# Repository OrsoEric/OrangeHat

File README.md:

# OrangeHat
Raspberry Pi Hat

**TPS55386 Board**  
Dual buck from 2S to 4S LIPO to two 3.0A channels.  

**OrangeHat**  
Assembly

Demo OrangeHat installed on Maze Runner (click on image to see video on youtube)    

**OrangeHat Firmware**  
LCD Display (click on image to see video on youtube)  

Eight Servomotors Demo

https://github.com/user-attachments/assets/cbe1ea65-5b8f-492d-bec4-1e71fcff2395

**OrangeHat Software**  
NODE.JS Webserver video streaming and serial communication (click on image to see video on youtube)

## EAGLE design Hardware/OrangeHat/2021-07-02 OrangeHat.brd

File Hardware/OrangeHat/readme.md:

**FEATURES**  
- XT60 power connector
- TPS55386 Dual Buck two 5.2V3.0A channels. Reverse voltage protection. Passive and active overcurrent protection.
- Full power monitor. Three voltages, Three currents.
- Raspberry Pi GPIO (10pins) UART and RESET (for bootloader)
- AT4809 microcontroller with UPDI programming
- One user button. Two user LEDs-
- 16x2 LCD screen
- RS485 commuinication over 3.5mm Jack audio cables.
- 8x Servo channels
- Onboard Waveshare 10DOF IMU

**Schematics**  

**PCB Render**  
Render of PCB, Top and Bot side.  
  
Render of the gerbers files.  

**Microcontroller Pin Assignment Table**

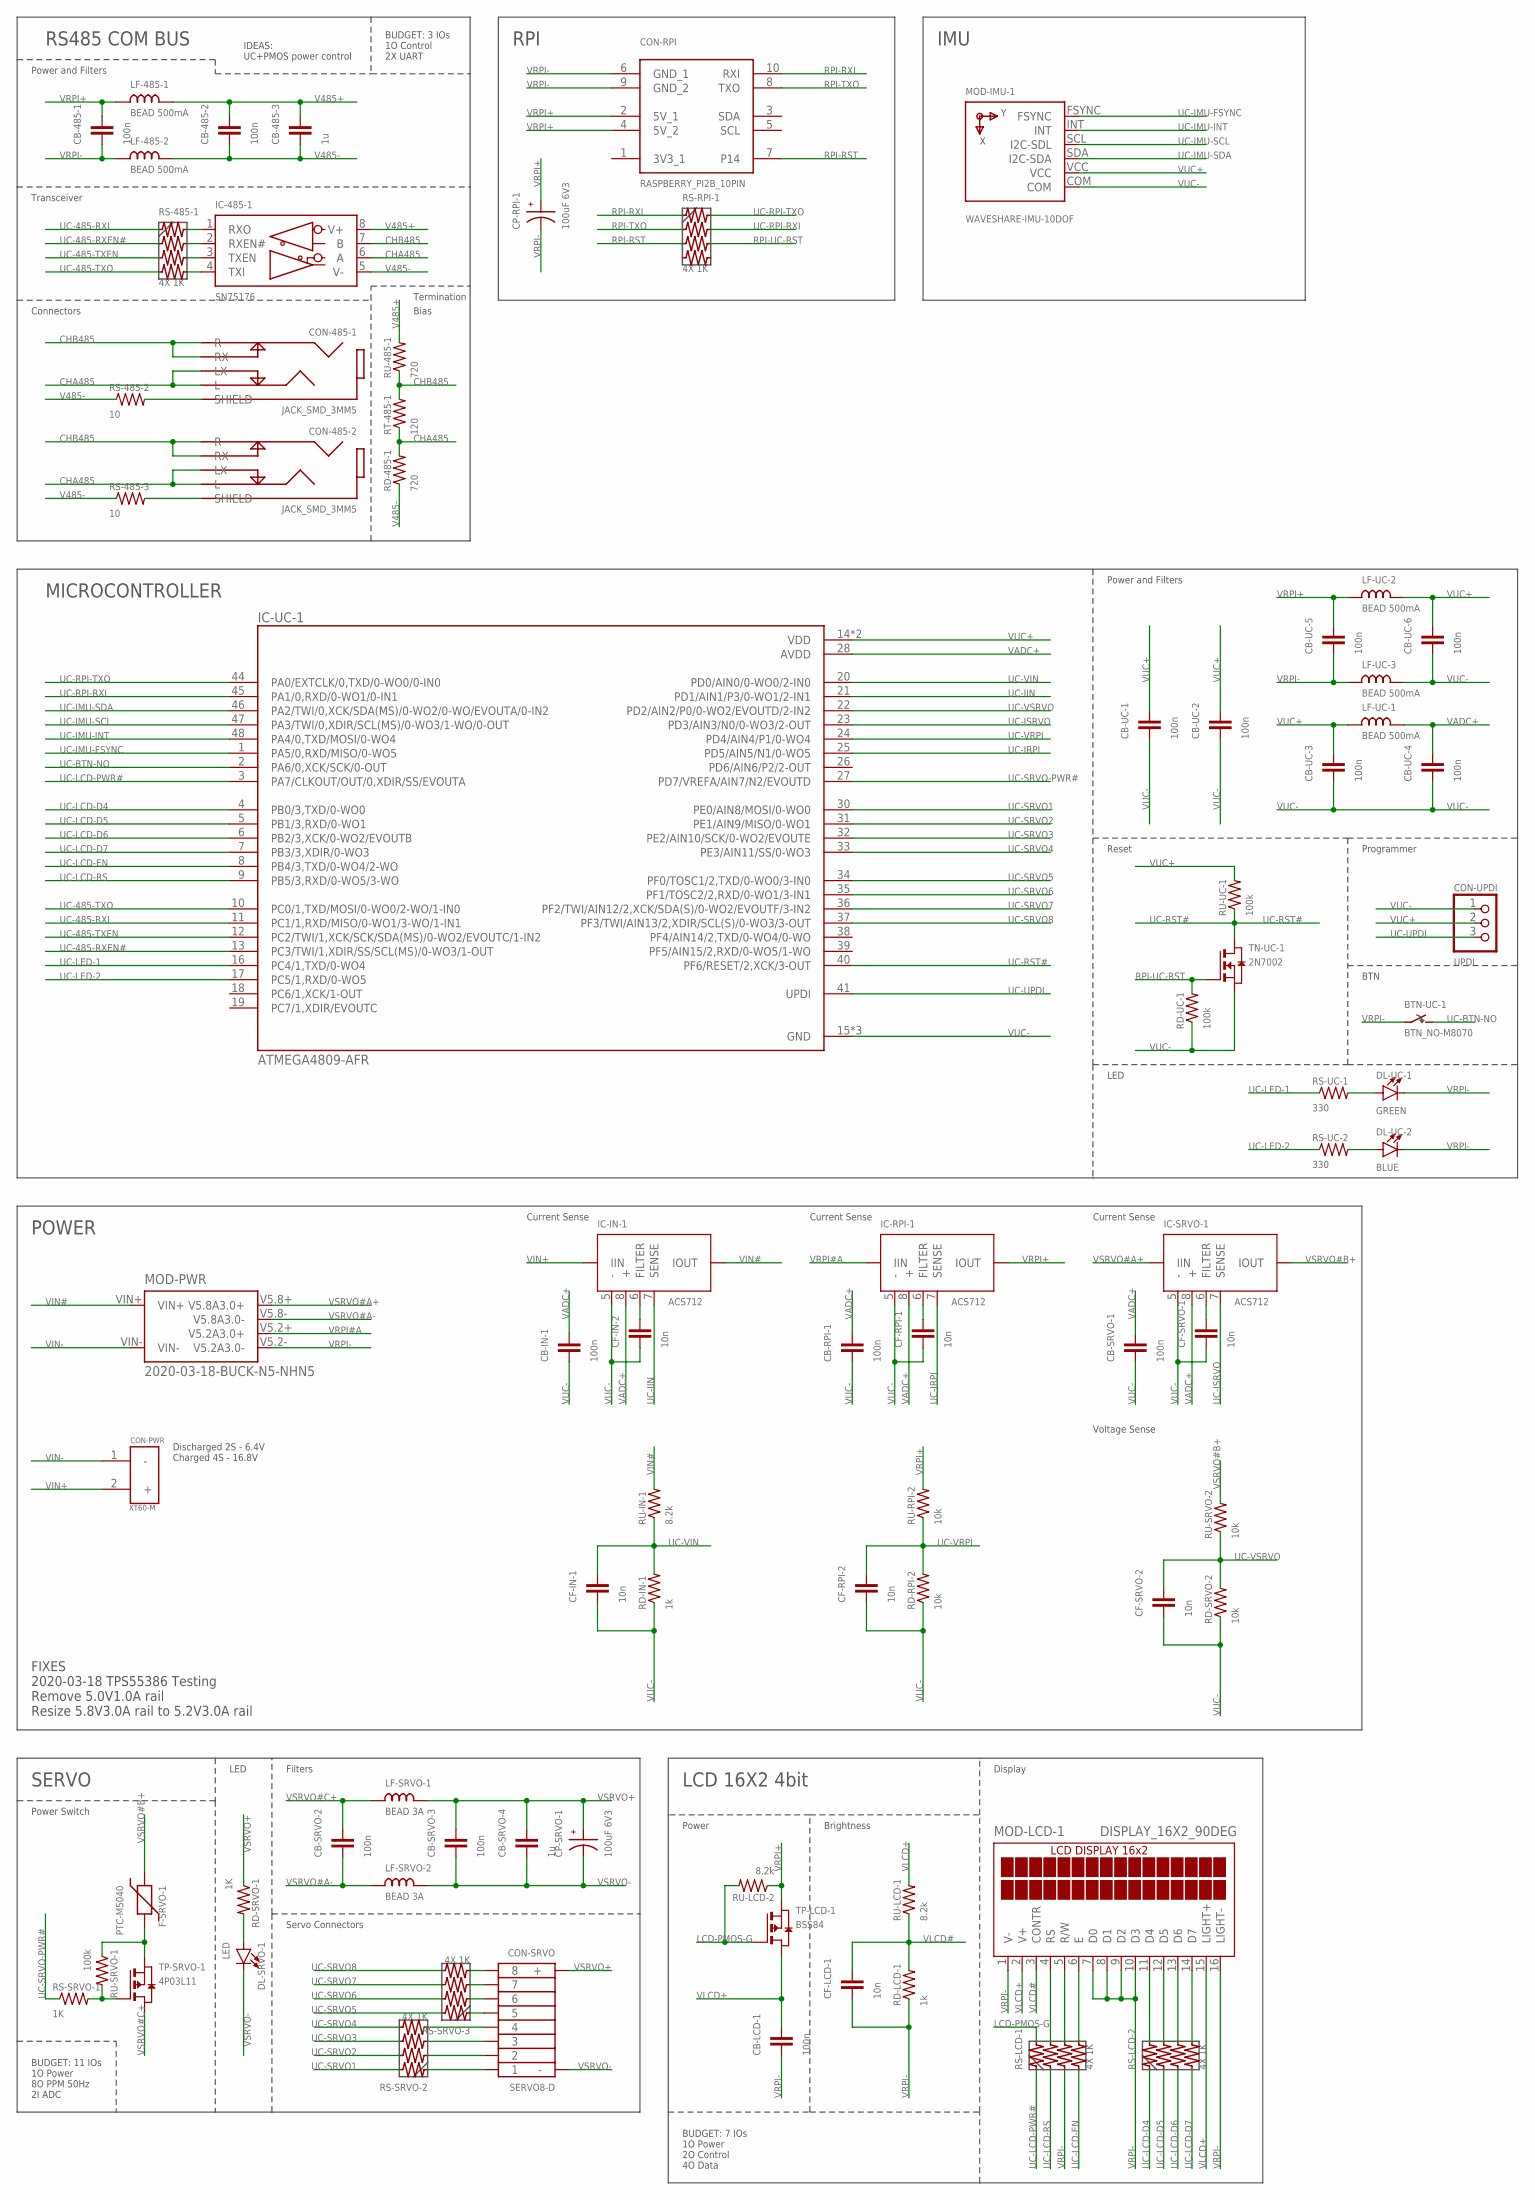
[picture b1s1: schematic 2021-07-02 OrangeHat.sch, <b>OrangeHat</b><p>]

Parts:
BTN-UC-1: BTN_NO-M8070; SMD_BTN_M8070
CB-485-1, CB-485-2: 100n; SMD-M2012
CB-485-3: 1u; SMD-M2012
CB-IN-1: 100n; SMD-M2012
CB-LCD-1: 100n; SMD-M2012
CB-RPI-1: 100n; SMD-M2012
CB-SRVO-1, CB-SRVO-2, CB-SRVO-3: 100n; SMD-M2012
CB-SRVO-4: 1u; SMD-M2012
CB-UC-1, CB-UC-2, CB-UC-3, CB-UC-4, CB-UC-5, CB-UC-6: 100n; SMD-M2012
CF-IN-1, CF-IN-2: 10n; SMD-M2012
CF-LCD-1: 10n; SMD-M2012
CF-RPI-1, CF-RPI-2: 10n; SMD-M2012
CF-SRVO-1, CF-SRVO-2: 10n; SMD-M2012
CON-485-1, CON-485-2: JACK_SMD_3MM5
CON-PWR: XT60-M; AMASS_XT60-M
CON-RPI: RASPBERRY_PI2B_10PIN
CON-SRVO: SERVO8-D; SERVO8#
CON-UPDI: UPDI; 1X03
CP-RPI-1: 100uF 6V3; E2,5-5
CP-SRVO-1: 100uF 6V3; E2,5-5
DL-SRVO-1: LED; SMD-M2012-POL
DL-UC-1: GREEN; SMD-M2012-POL
DL-UC-2: BLUE; SMD-M2012-POL
F-SRVO-1: PTC-M5040; SMD-M5040
IC-485-1: SN75176; DIL08
IC-IN-1: ACS712; SO8
IC-RPI-1: ACS712; SO8
IC-SRVO-1: ACS712; SO8
IC-UC-1: ATMEGA4809-AFR; QFP50P900X900X120-48N
LF-485-1, LF-485-2: BEAD 500mA; SMD-M2012
LF-SRVO-1, LF-SRVO-2: BEAD 3A; SMD-M2016
LF-UC-1, LF-UC-2, LF-UC-3: BEAD 500mA; SMD-M2012
MOD-IMU-1: WAVESHARE-IMU-10DOF
MOD-LCD-1: DISPLAY_16X2_90DEG
MOD-PWR: 2020-03-18-BUCK-N5-NHN5; 2020-03-18-BUCK-NHN5
RD-485-1: 720; TH-2MM54-V
RD-IN-1: 1k; SMD-M2012
RD-LCD-1: 1k; SMD-M2012
RD-RPI-2: 10k; SMD-M2012
RD-SRVO-1: 1K; SMD-M2012
RD-SRVO-2: 10k; SMD-M2012
RD-UC-1: 100k; SMD-M2012
RS-485-1: 4X 1K; RAC1206
RS-485-2, RS-485-3: 10; SMD-M2012
RS-LCD-1, RS-LCD-2: 4X 1K; RAC1206
RS-RPI-1: 4X 1K; RAC1206
RS-SRVO-1: 1K; SMD-M2012
RS-SRVO-2, RS-SRVO-3: 4X 1K; RAC1206
RS-UC-1, RS-UC-2: 330; SMD-M2012
RT-485-1: 120; TH-2MM54-V
RU-485-1: 720; TH-2MM54-V
RU-IN-1: 8.2k; SMD-M2012
RU-LCD-1, RU-LCD-2: 8.2k; SMD-M2012
RU-RPI-2: 10k; SMD-M2012
RU-SRVO-1: 100k; SMD-M2012
RU-SRVO-2: 10k; SMD-M2012
RU-UC-1: 100k; SMD-M2012
TN-UC-1: 2N7002; SOT23
TP-LCD-1: BSS84; SOT23
TP-SRVO-1: 4P03L11; TO252

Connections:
3V3_1: CON-RPI.1 (3V3_1)
CHA485: CON-485-1.L, CON-485-1.LX, CON-485-2.L, CON-485-2.LX, IC-485-1.6 (A), RD-485-1.2, RT-485-1.1
CHB485: CON-485-1.R, CON-485-1.RX, CON-485-2.R, CON-485-2.RX, IC-485-1.7 (B), RT-485-1.2, RU-485-1.1
LCD-PMOS-G: RS-LCD-1.1B, RU-LCD-2.2, TP-LCD-1.1 (G)
unnamed: CF-RPI-1.2, IC-RPI-1.6 (FILTER)
unnamed: CF-IN-2.2, IC-IN-1.6 (FILTER)
unnamed: MOD-LCD-1.5 (R/W), RS-LCD-1.3B
unnamed: DL-UC-1.+, RS-UC-1.2
unnamed: RS-SRVO-1.2, RU-SRVO-1.2, TP-SRVO-1.1 (G)
unnamed: F-SRVO-1.2, RU-SRVO-1.1, TP-SRVO-1.2 (S)
unnamed: MOD-LCD-1.4 (RS), RS-LCD-1.2B
unnamed: MOD-LCD-1.6 (E), RS-LCD-1.4B
unnamed: MOD-LCD-1.11 (D4), RS-LCD-2.1B
unnamed: MOD-LCD-1.12 (D5), RS-LCD-2.2B
unnamed: MOD-LCD-1.13 (D6), RS-LCD-2.3B
unnamed: MOD-LCD-1.14 (D7), RS-LCD-2.4B
unnamed: DL-UC-2.+, RS-UC-2.2
unnamed: IC-485-1.1 (RXO), RS-485-1.1B
unnamed: IC-485-1.2 (RXEN#), RS-485-1.2B
unnamed: CF-SRVO-1.2, IC-SRVO-1.6 (FILTER)
unnamed: DL-SRVO-1.+, RD-SRVO-1.2
unnamed: CON-SRVO.8, RS-SRVO-3.4A
unnamed: CON-SRVO.7, RS-SRVO-3.3A
unnamed: CON-SRVO.6, RS-SRVO-3.2A
unnamed: CON-SRVO.5, RS-SRVO-3.1A
unnamed: CON-SRVO.4, RS-SRVO-2.4A
unnamed: CON-SRVO.3, RS-SRVO-2.3A
unnamed: CON-SRVO.2, RS-SRVO-2.2A
unnamed: CON-SRVO.1, RS-SRVO-2.1A
unnamed: IC-485-1.3 (TXEN), RS-485-1.3B
unnamed: IC-485-1.4 (TXI), RS-485-1.4B
unnamed: CON-485-1.SHIELD, RS-485-2.2
unnamed: CON-485-2.SHIELD, RS-485-3.2
RPI-RST: CON-RPI.7 (P14), RS-RPI-1.3A
RPI-RXI: CON-RPI.10 (RXI), RS-RPI-1.1A
RPI-TXO: CON-RPI.8 (TXO), RS-RPI-1.2A
RPI-UC-RST: RD-UC-1.2, RS-RPI-1.3B, TN-UC-1.1 (G)
UC-485-RXEN#: IC-UC-1.13 (PC3/TWI/1,XDIR/SS/SCL(MS)/0-WO3/1-OUT), RS-485-1.2A
UC-485-RXI: IC-UC-1.11 (PC1/1,RXD/MISO/0-WO1/3-WO/1-IN1), RS-485-1.1A
UC-485-TXEN: IC-UC-1.12 (PC2/TWI/1,XCK/SCK/SDA(MS)/0-WO2/EVOUTC/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), RS-485-1.3A
UC-485-TXO: IC-UC-1.10 (PC0/1,TXD/MOSI/0-WO0/2-WO/1-IN0), RS-485-1.4A
UC-BTN-NO: BTN-UC-1.2B, BTN-UC-1.3B, IC-UC-1.2 (PA6/0,XCK/SCK/0-OUT)
UC-IIN: IC-IN-1.7 (SENSE), IC-UC-1.21 (PD1/AIN1/P3/0-WO1/2-IN1)
UC-IMU-FSYNC: IC-UC-1.1 (PA5/0,RXD/MISO/0-WO5), MOD-IMU-1.FSYNC
UC-IMU-INT: IC-UC-1.48 (PA4/0,TXD/MOSI/0-WO4), MOD-IMU-1.INT
UC-IMU-SCL: IC-UC-1.47 (PA3/TWI/0,XDIR/SCL(MS)/0-WO3/1-WO/0-OUT), MOD-IMU-1.SCL (I2C-SDL)
UC-IMU-SDA: IC-UC-1.46 (PA2/TWI/0,XCK/SDA(MS)/0-WO2/0-WO/EVOUTA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), MOD-IMU-1.SDA (I2C-SDA)
UC-IRPI: IC-RPI-1.7 (SENSE), IC-UC-1.25 (PD5/AIN5/N1/0-WO5)
UC-ISRVO: IC-SRVO-1.7 (SENSE), IC-UC-1.23 (PD3/AIN3/N0/0-WO3/2-OUT)
UC-LCD-D4: IC-UC-1.4 (PB0/3,TXD/0-WO0), RS-LCD-2.1A
UC-LCD-D5: IC-UC-1.5 (PB1/3,RXD/0-WO1), RS-LCD-2.2A
UC-LCD-D6: IC-UC-1.6 (PB2/3,XCK/0-WO2/EVOUTB), RS-LCD-2.3A
UC-LCD-D7: IC-UC-1.7 (PB3/3,XDIR/0-WO3), RS-LCD-2.4A
UC-LCD-EN: IC-UC-1.8 (PB4/3,TXD/0-WO4/2-WO), RS-LCD-1.4A
UC-LCD-PWR#: IC-UC-1.3 (PA7/CLKOUT/OUT/0,XDIR/SS/EVOUTA), RS-LCD-1.1A
UC-LCD-RS: IC-UC-1.9 (PB5/3,RXD/0-WO5/3-WO), RS-LCD-1.2A
UC-LED-1: IC-UC-1.16 (PC4/1,TXD/0-WO4), RS-UC-1.1
UC-LED-2: IC-UC-1.17 (PC5/1,RXD/0-WO5), RS-UC-2.1
UC-RPI-RXI: IC-UC-1.45 (PA1/0,RXD/0-WO1/0-IN1), RS-RPI-1.2B
UC-RPI-TXO: IC-UC-1.44 (PA0/EXTCLK/0,TXD/0-WO0/0-IN0), RS-RPI-1.1B
UC-RST#: IC-UC-1.40 (PF6/RESET/2,XCK/3-OUT), RU-UC-1.1, TN-UC-1.3 (D)
UC-SRVO1: IC-UC-1.30 (PE0/AIN8/MOSI/0-WO0), RS-SRVO-2.1B
UC-SRVO2: IC-UC-1.31 (PE1/AIN9/MISO/0-WO1), RS-SRVO-2.2B
UC-SRVO3: IC-UC-1.32 (PE2/AIN10/SCK/0-WO2/EVOUTE), RS-SRVO-2.3B
UC-SRVO4: IC-UC-1.33 (PE3/AIN11/SS/0-WO3), RS-SRVO-2.4B
UC-SRVO5: IC-UC-1.34 (PF0/TOSC1/2,TXD/0-WO0/3-IN0), RS-SRVO-3.1B
UC-SRVO6: IC-UC-1.35 (PF1/TOSC2/2,RXD/0-WO1/3-IN1), RS-SRVO-3.2B
UC-SRVO7: IC-UC-1.36 (PF2/TWI/AIN12/2,XCK/SDA(S)/0-WO2/EVOUTF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), RS-SRVO-3.3B
UC-SRVO8: IC-UC-1.37 (PF3/TWI/AIN13/2,XDIR/SCL(S)/0-WO3/3-OUT), RS-SRVO-3.4B
UC-SRVO-PWR#: IC-UC-1.27 (PD7/VREFA/AIN7/N2/EVOUTD), RS-SRVO-1.1
UC-UPDI: CON-UPDI.3, IC-UC-1.41 (UPDI)
UC-VIN: CF-IN-1.2, IC-UC-1.20 (PD0/AIN0/0-WO0/2-IN0), RD-IN-1.2, RU-IN-1.1
UC-VRPI: CF-RPI-2.2, IC-UC-1.24 (PD4/AIN4/P1/0-WO4), RD-RPI-2.2, RU-RPI-2.1
UC-VSRVO: CF-SRVO-2.2, IC-UC-1.22 (PD2/AIN2/P0/0-WO2/EVOUTD/2-IN2), RD-SRVO-2.2, RU-SRVO-2.1
V485+: CB-485-2.2, CB-485-3.2, IC-485-1.8 (V+), LF-485-1.2, RU-485-1.2
V485-: CB-485-2.1, CB-485-3.1, IC-485-1.5 (V-), LF-485-2.2, RD-485-1.1, RS-485-2.1, RS-485-3.1
VADC+: CB-IN-1.2, CB-RPI-1.2, CB-SRVO-1.2, CB-UC-4.2, IC-IN-1.8 (+), IC-RPI-1.8 (+), IC-SRVO-1.8 (+), IC-UC-1.28 (AVDD), LF-UC-1.2
VIN#: IC-IN-1.3 (IOUT), IC-IN-1.4 (IOUT), MOD-PWR.VIN+, RU-IN-1.2
VIN+: CON-PWR.2 (+), IC-IN-1.1 (IIN), IC-IN-1.2 (IIN)
VIN-: CON-PWR.1 (-), MOD-PWR.VIN-
VLCD#: CF-LCD-1.2, MOD-LCD-1.3 (CONTR), RD-LCD-1.2, RU-LCD-1.1
VLCD+: CB-LCD-1.2, MOD-LCD-1.2 (V+), MOD-LCD-1.15 (LIGHT+), RU-LCD-1.2, TP-LCD-1.3 (D)
VRPI#A: IC-RPI-1.1 (IIN), IC-RPI-1.2 (IIN), MOD-PWR.V5.2+ (V5.2A3.0+)
VRPI+: CB-485-1.2, CB-UC-5.2, CON-RPI.2 (5V_1), CON-RPI.4 (5V_2), CP-RPI-1.+, IC-RPI-1.3 (IOUT), IC-RPI-1.4 (IOUT), LF-485-1.1, LF-UC-2.1, RU-LCD-2.1, RU-RPI-2.2, TP-LCD-1.2 (S)
VRPI-: BTN-UC-1.1A, BTN-UC-1.4A, CB-485-1.1, CB-LCD-1.1, CB-UC-5.1, CF-LCD-1.1, CON-RPI.6 (GND_1), CON-RPI.9 (GND_2), CP-RPI-1.-, DL-UC-1.-, DL-UC-2.-, LF-485-2.1, LF-UC-3.1, MOD-LCD-1.1 (V-), MOD-LCD-1.7 (D0), MOD-LCD-1.8 (D1), MOD-LCD-1.9 (D2), MOD-LCD-1.10 (D3), MOD-LCD-1.16 (LIGHT-), MOD-PWR.V5.2- (V5.2A3.0-), RD-LCD-1.1, RS-LCD-1.3A
VSRVO#A+: IC-SRVO-1.1 (IIN), IC-SRVO-1.2 (IIN), MOD-PWR.V5.8+ (V5.8A3.0+)
VSRVO#A-: CB-SRVO-2.1, LF-SRVO-2.1, MOD-PWR.V5.8- (V5.8A3.0-)
VSRVO#B+: F-SRVO-1.1, IC-SRVO-1.3 (IOUT), IC-SRVO-1.4 (IOUT), RU-SRVO-2.2
VSRVO#C+: CB-SRVO-2.2, LF-SRVO-1.1, TP-SRVO-1.3 (D)
VSRVO+: CB-SRVO-3.2, CB-SRVO-4.2, CON-SRVO.1+ (+), CON-SRVO.2+ (+), CON-SRVO.3+ (+), CON-SRVO.4+ (+), CON-SRVO.5+ (+), CON-SRVO.6+ (+), CON-SRVO.7+ (+), CON-SRVO.8+ (+), CP-SRVO-1.+, LF-SRVO-1.2, RD-SRVO-1.1
VSRVO-: CB-SRVO-3.1, CB-SRVO-4.1, CON-SRVO.1- (-), CON-SRVO.2- (-), CON-SRVO.3- (-), CON-SRVO.4- (-), CON-SRVO.5- (-), CON-SRVO.6- (-), CON-SRVO.7- (-), CON-SRVO.8- (-), CP-SRVO-1.-, DL-SRVO-1.-, LF-SRVO-2.2
VUC+: CB-UC-1.2, CB-UC-2.2, CB-UC-3.2, CB-UC-6.2, CON-UPDI.2, IC-UC-1.14 (VDD), IC-UC-1.42 (VDD), LF-UC-1.1, LF-UC-2.2, MOD-IMU-1.VCC, RU-UC-1.2
VUC-: CB-IN-1.1, CB-RPI-1.1, CB-SRVO-1.1, CB-UC-1.1, CB-UC-2.1, CB-UC-3.1, CB-UC-4.1, CB-UC-6.1, CF-IN-1.1, CF-IN-2.1, CF-RPI-1.1, CF-RPI-2.1, CF-SRVO-1.1, CF-SRVO-2.1, CON-UPDI.1, IC-IN-1.5 (-), IC-RPI-1.5 (-), IC-SRVO-1.5 (-), IC-UC-1.15 (GND), IC-UC-1.29 (GND), IC-UC-1.43 (GND), LF-UC-3.2, MOD-IMU-1.COM, RD-IN-1.1, RD-RPI-2.1, RD-SRVO-2.1, RD-UC-1.1, TN-UC-1.2 (S)

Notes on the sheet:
LCD 16X2 4bit
Power
Brightness
Display
BUDGET: 7 IOs 1O Power 2O Control 4O Data
SERVO
BUDGET: 11 IOs 1O Power 8O PPM 50Hz 2I ADC
Servo Connectors
Power Switch
Filters
Current Sense
Voltage Sense
LED
RS485 COM BUS
Power and Filters
Transceiver
Connectors
Termination
Bias
BUDGET: 3 IOs 1O Control 2X UART
IDEAS: UC+PMOS power control
MICROCONTROLLER
Reset
RPI
POWER
Programmer
FIXES 2020-03-18 TPS55386 Testing Remove 5.0V1.0A rail Resize 5.8V3.0A rail to 5.2V3.0A rail
BTN
IMU
Discharged 2S - 6.4V Charged 4S - 16.8V

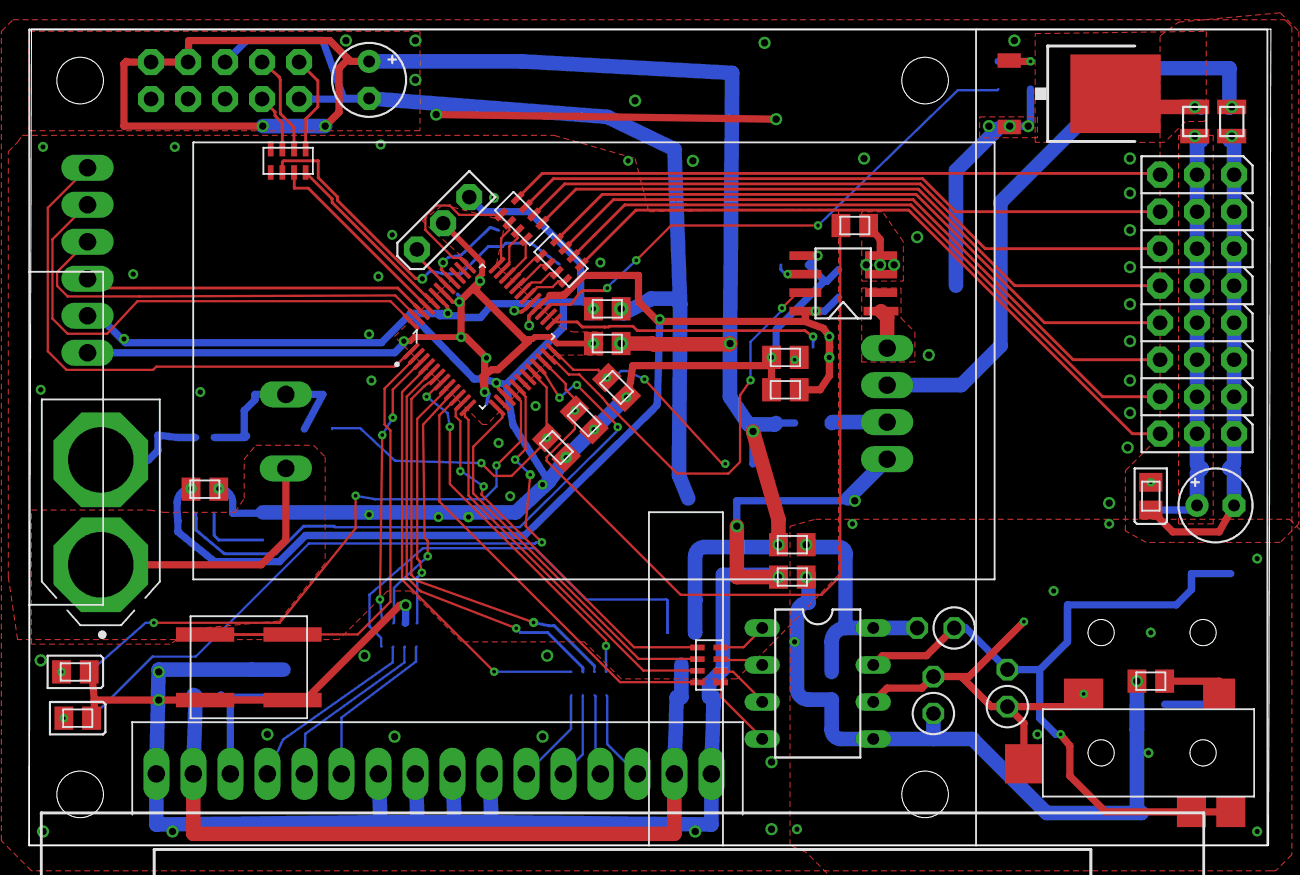
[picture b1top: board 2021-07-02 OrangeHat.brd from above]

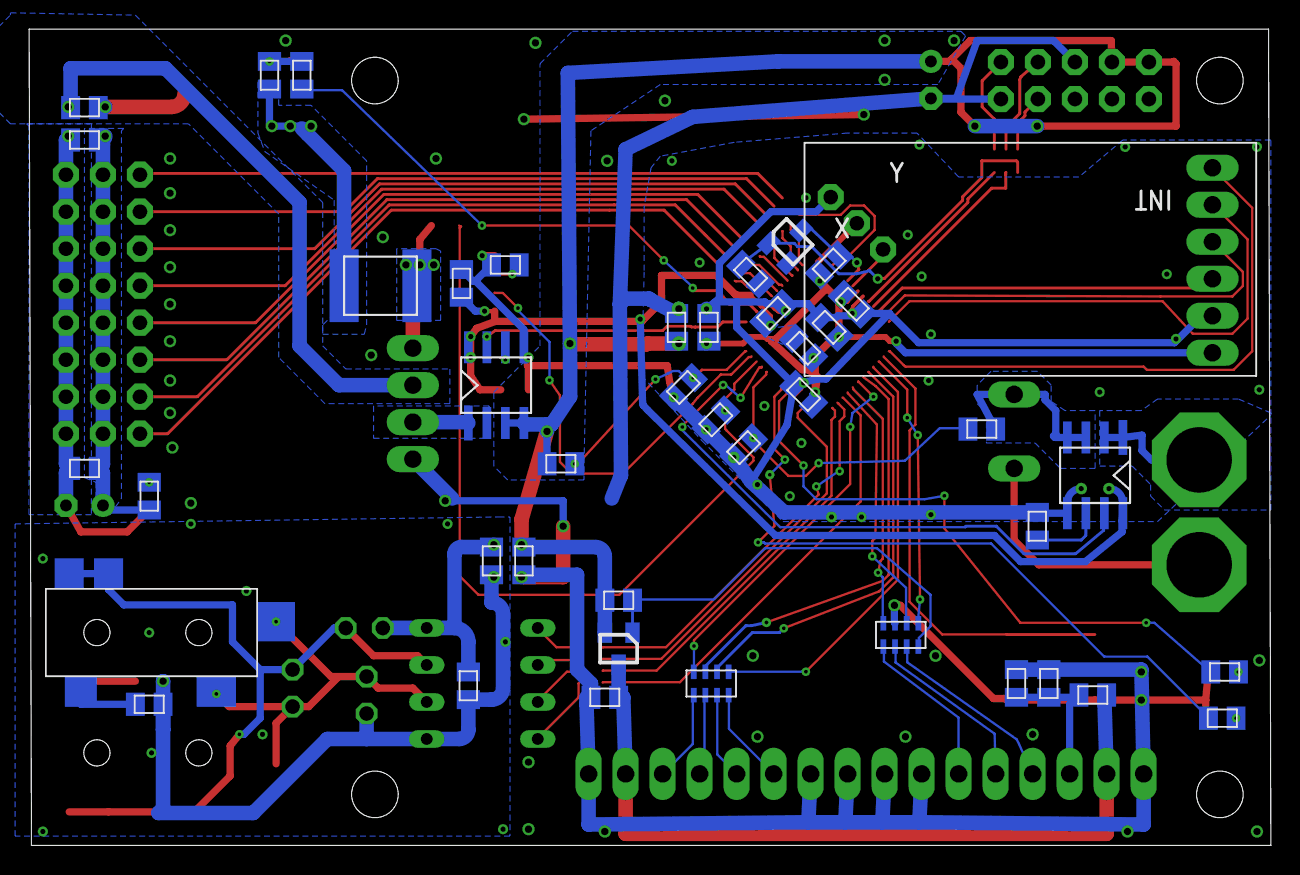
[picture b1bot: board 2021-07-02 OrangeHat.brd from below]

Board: 2 copper layers, 85.2 x 56.0 mm, 83 parts (43 on the bottom side), 92 nets.

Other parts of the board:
U$1: SIGNATURE_ADROBOT_SMALL
U$2: SIGNATURE_ORANGEBOT_SMALL

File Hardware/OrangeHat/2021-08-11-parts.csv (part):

"Part";"Value";"Device";"Package";"Description";"AVAILABILITY";"DESCRIPTION";"MF";"MP";"MPN";"OC_FARNELL";"OC_NEWARK";"PACKAGE";"PRICE";
"BTN-UC-1";"BTN_NO-M8070";"BTN_NO-M8070";"SMD_BTN_M8070";"Push Button";"";"";"";"";"";"";"";"";"";
"CB-485-1";"100n";"C-NPOL";"SMD-M2012";"CAPACITOR, European symbol";"";"";"";"";"";"";"";"";"";
"CB-485-2";"100n";"C-NPOL";"SMD-M2012";"CAPACITOR, European symbol";"";"";"";"";"";"";"";"";"";
"CB-485-3";"1u";"C-NPOL";"SMD-M2012";"CAPACITOR, European symbol";"";"";"";"";"";"";"";"";"";
"CB-IN-1";"100n";"C-NPOL";"SMD-M2012";"CAPACITOR, European symbol";"";"";"";"";"";"";"";"";"";
"CB-LCD-1";"100n";"C-NPOL";"SMD-M2012";"CAPACITOR, European symbol";"";"";"";"";"";"";"";"";"";
"CB-RPI-1";"100n";"C-NPOL";"SMD-M2012";"CAPACITOR, European symbol";"";"";"";"";"";"";"";"";"";
"CB-SRVO-1";"100n";"C-NPOL";"SMD-M2012";"CAPACITOR, European symbol";"";"";"";"";"";"";"";"";"";
"CB-SRVO-2";"100n";"C-NPOL";"SMD-M2012";"CAPACITOR, European symbol";"";"";"";"";"";"";"";"";"";
"CB-SRVO-3";"100n";"C-NPOL";"SMD-M2012";"CAPACITOR, European symbol";"";"";"";"";"";"";"";"";"";
"CB-SRVO-4";"1u";"C-NPOL";"SMD-M2012";"CAPACITOR, European symbol";"";"";"";"";"";"";"";"";"";
"CB-UC-1";"100n";"C-NPOL";"SMD-M2012";"CAPACITOR, European symbol";"";"";"";"";"";"";"";"";"";
"CB-UC-2";"100n";"C-NPOL";"SMD-M2012";"CAPACITOR, European symbol";"";"";"";"";"";"";"";"";"";
"CB-UC-3";"100n";"C-NPOL";"SMD-M2012";"CAPACITOR, European symbol";"";"";"";"";"";"";"";"";"";
"CB-UC-4";"100n";"C-NPOL";"SMD-M2012";"CAPACITOR, European symbol";"";"";"";"";"";"";"";"";"";
"CB-UC-5";"100n";"C-NPOL";"SMD-M2012";"CAPACITOR, European symbol";"";"";"";"";"";"";"";"";"";
"CB-UC-6";"100n";"C-NPOL";"SMD-M2012";"CAPACITOR, European symbol";"";"";"";"";"";"";"";"";"";
"CF-IN-1";"10n";"C-NPOL";"SMD-M2012";"CAPACITOR, European symbol";"";"";"";"";"";"";"";"";"";
"CF-IN-2";"10n";"C-NPOL";"SMD-M2012";"CAPACITOR, European symbol";"";"";"";"";"";"";"";"";"";
"CF-LCD-1";"10n";"C-NPOL";"SMD-M2012";"CAPACITOR, European symbol";"";"";"";"";"";"";"";"";"";
"CF-RPI-1";"10n";"C-NPOL";"SMD-M2012";"CAPACITOR, European symbol";"";"";"";"";"";"";"";"";"";
"CF-RPI-2";"10n";"C-NPOL";"SMD-M2012";"CAPACITOR, European symbol";"";"";"";"";"";"";"";"";"";
"CF-SRVO-1";"10n";"C-NPOL";"SMD-M2012";"CAPACITOR, European symbol";"";"";"";"";"";"";"";"";"";
"CF-SRVO-2";"10n";"C-NPOL";"SMD-M2012";"CAPACITOR, European symbol";"";"";"";"";"";"";"";"";"";
"CON-485-1";"JACK_SMD_3MM5";"JACK_SMD_3MM5";"JACK_SMD_3MM5";"Jack 3.5mm";"";"";"";"";"";"";"";"";"";
"CON-485-2";"JACK_SMD_3MM5";"JACK_SMD_3MM5";"JACK_SMD_3MM5";"Jack 3.5mm";"";"";"";"";"";"";"";"";"";
"CON-PWR";"XT60-M";"XT60-M";"AMASS_XT60-M";"DC supply; XT60; male; PIN:2; for cable; soldered; 60A; 500V";"Unavailable";" ";"AMASS";"XT60-M";"";"";"";"Package Analog Devices";"None";
"CON-RPI";"RASPBERRY_PI2B_10PIN";"RASPBERRY_PI2B_10PIN";"RASPBERRY_PI2B_10PIN";"Raspberry Pi 2B/3B Hat Footprint";"";"";"";"";"";"";"";"";"";
"CON-SRVO";"SERVO8-D";"SERVO8-D";"SERVO8#";"SERVO";"";"";"";"";"";"";"";"";"";
"CON-UPDI";"UPDI";"PINHD-1X3";"1X03";"PIN HEADER";"";"";"";"";"";"";"";"";"";
"CP-RPI-1";"100uF 6V3";"C-POLE2.5-5";"E2,5-5";"POLARIZED CAPACITOR, American symbol";"";"";"";"";"";"";"";"";"";
"CP-SRVO-1";"100uF 6V3";"C-POLE2.5-5";"E2,5-5";"POLARIZED CAPACITOR, American symbol";"";"";"";"";"";"";"";"";"";
"DL-SRVO-1";"LED";"LED";"SMD-M2012-POL";"Standard LED";"";"";"";"";"";"";"";"";"";
"DL-UC-1";"GREEN";"LED";"SMD-M2012-POL";"Standard LED";"";"";"";"";"";"";"";"";"";
"DL-UC-2";"BLUE";"LED";"SMD-M2012-POL";"Standard LED";"";"";"";"";"";"";"";"";"";
"F-SRVO-1";"PTC-M5040";"PTC-M5040";"SMD-M5040";"Resettable Fuse PTC";"";"";"";"";"";"";"";"";"";
"IC-485-1";"SN75176";"RS485";"DIL08";"RS485 TRANSEIVER";"";"";"";"";"MAX481CPA+";"unknown";"99K3445";"";"";
"IC-IN-1";"ACS712";"ACS712";"SO8";"ACS712-{X}";"";"";"";"";"";"";"";"";"";
"IC-RPI-1";"ACS712";"ACS712";"SO8";"ACS712-{X}";"";"";"";"";"";"";"";"";"";
"IC-SRVO-1";"ACS712";"ACS712";"SO8";"ACS712-{X}";"";"";"";"";"";"";"";"";"";
"IC-UC-1";"ATMEGA4809-AFR";"ATMEGA4809-AFR";"QFP50P900X900X120-48N";"20MHz 48KB TQFP48 Ind 125C Green T&R";"Unavailable";" 20MHz 48KB TQFP48 Ind 125C Green T&R ";"Microchip";"ATMEGA4809-AFR";"";"";"";"TQFP-48 Microchip";"None";
"LF-485-1";"BEAD 500mA";"L-M2012";"SMD-M2012";"INDUCTOR, American symbol";"";"";"";"";"";"";"";"";"";
"LF-485-2";"BEAD 500mA";"L-M2012";"SMD-M2012";"INDUCTOR, American symbol";"";"";"";"";"";"";"";"";"";
"LF-SRVO-1";"BEAD 3A";"L-M2016";"SMD-M2016";"INDUCTOR, American symbol";"";"";"";"";"";"";"";"";"";
"LF-SRVO-2";"BEAD 3A";"L-M2016";"SMD-M2016";"INDUCTOR, American symbol";"";"";"";"";"";"";"";"";"";
"LF-UC-1";"BEAD 500mA";"L-M2012";"SMD-M2012";"INDUCTOR, American symbol";"";"";"";"";"";"";"";"";"";
"LF-UC-2";"BEAD 500mA";"L-M2012";"SMD-M2012";"INDUCTOR, American symbol";"";"";"";"";"";"";"";"";"";
"LF-UC-3";"BEAD 500mA";"L-M2012";"SMD-M2012";"INDUCTOR, American symbol";"";"";"";"";"";"";"";"";"";
"MOD-IMU-1";"WAVESHARE-IMU-10DOF";"WAVESHARE-IMU-10DOF";"WAVESHARE-IMU-10DOF";"WaveShare IMU 10DOF";"";"";"";"";"";"";"";"";"";
"MOD-LCD-1";"DISPLAY_16X2_90DEG";"DISPLAY_16X2_90DEG";"DISPLAY_16X2_90DEG";"Display 16X2";"";"";"";"";"";"";"";"";"";
"MOD-PWR";"2020-03-18-BUCK-N5-NHN5";"2020-03-18-BUCK-N5-NHN5";"2020-03-18-BUCK-NHN5";"2020-03-18 Buck Module";"";"";"";"";"";"";"";"";"";
"RD-485-1";"720";"R0207/2V";"TH-2MM54-V";"RESISTOR, American symbol";"";"";"";"";"";"";"";"";"";
"RD-IN-1";"1k";"R-M2012";"SMD-M2012";"RESISTOR, American symbol";"";"";"";"";"";"";"";"";"";
"RD-LCD-1";"1k";"R-M2012";"SMD-M2012";"RESISTOR, American symbol";"";"";"";"";"";"";"";"";"";
"RD-RPI-2";"10k";"R-M2012";"SMD-M2012";"RESISTOR, American symbol";"";"";"";"";"";"";"";"";"";
"RD-SRVO-1";"1K";"R-M2012";"SMD-M2012";"RESISTOR, American symbol";"";"";"";"";"";"";"";"";"";
"RD-SRVO-2";"10k";"R-M2012";"SMD-M2012";"RESISTOR, American symbol";"";"";"";"";"";"";"";"";"";
"RD-UC-1";"100k";"R-M2012";"SMD-M2012";"RESISTOR, American symbol";"";"";"";"";"";"";"";"";"";
"RS-485-1";"4X 1K";"RAC164";"RAC1206";"Resistor Array of four elements";"";"";"";"";"";"";"";"";"";
"RS-485-2";"10";"R-M2012";"SMD-M2012";"RESISTOR, American symbol";"";"";"";"";"";"";"";"";"";
"RS-485-3";"10";"R-M2012";"SMD-M2012";"RESISTOR, American symbol";"";"";"";"";"";"";"";"";"";
"RS-LCD-1";"4X 1K";"RAC164";"RAC1206";"Resistor Array of four elements";"";"";"";"";"";"";"";"";"";
"RS-LCD-2";"4X 1K";"RAC164";"RAC1206";"Resistor Array of four elements";"";"";"";"";"";"";"";"";"";
"RS-RPI-1";"4X 1K";"RAC164";"RAC1206";"Resistor Array of four elements";"";"";"";"";"";"";"";"";"";
"RS-SRVO-1";"1K";"R-M2012";"SMD-M2012";"RESISTOR, American symbol";"";"";"";"";"";"";"";"";"";
"RS-SRVO-2";"4X 1K";"RAC164";"RAC1206";"Resistor Array of four elements";"";"";"";"";"";"";"";"";"";
"RS-SRVO-3";"4X 1K";"RAC164";"RAC1206";"Resistor Array of four elements";"";"";"";"";"";"";"";"";"";
"RS-UC-1";"330";"R-M2012";"SMD-M2012";"RESISTOR, American symbol";"";"";"";"";"";"";"";"";"";
"RS-UC-2";"330";"R-M2012";"SMD-M2012";"RESISTOR, American symbol";"";"";"";"";"";"";"";"";"";
"RT-485-1";"120";"R0207/2V";"TH-2MM54-V";"RESISTOR, American symbol";"";"";"";"";"";"";"";"";"";
"RU-485-1";"720";"R0207/2V";"TH-2MM54-V";"RESISTOR, American symbol";"";"";"";"";"";"";"";"";"";
"RU-IN-1";"8.2k";"R-M2012";"SMD-M2012";"RESISTOR, American symbol";"";"";"";"";"";"";"";"";"";
"RU-LCD-1";"8.2k";"R-M2012";"SMD-M2012";"RESISTOR, American symbol";"";"";"";"";"";"";"";"";"";
"RU-LCD-2";"8.2k";"R-M2012";"SMD-M2012";"RESISTOR, American symbol";"";"";"";"";"";"";"";"";"";
"RU-RPI-2";"10k";"R-M2012";"SMD-M2012";"RESISTOR, American symbol";"";"";"";"";"";"";"";"";"";
"RU-SRVO-1";"100k";"R-M2012";"SMD-M2012";"RESISTOR, American symbol";"";"";"";"";"";"";"";"";"";
"RU-SRVO-2";"10k";"R-M2012";"SMD-M2012";"RESISTOR, American symbol";"";"";"";"";"";"";"";"";"";
"RU-UC-1";"100k";"R-M2012";"SMD-M2012";"RESISTOR, American symbol";"";"";"";"";"";"";"";"";"";
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
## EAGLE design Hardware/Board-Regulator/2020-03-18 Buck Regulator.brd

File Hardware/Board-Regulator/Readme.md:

# Board Regulator Schamatics    

# Board Regulator PCB  
Output 1: 5.8V 3.0A  
Output 2: 5.2V 3.0A  
Output 3: 5.0V 1.0A  

Render:
Regulator PCB render:  

**Assembled Board**

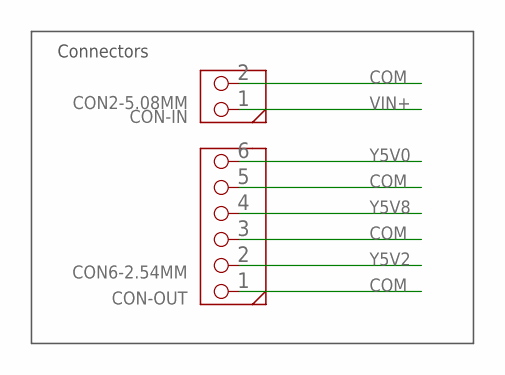
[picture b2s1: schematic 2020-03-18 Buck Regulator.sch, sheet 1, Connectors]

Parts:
CON-IN: CON2-5.08MM; CON2-508
CON-OUT: CON6-2.54MM; CON6

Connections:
COM: CON-IN.2, CON-OUT.1, CON-OUT.3, CON-OUT.5; also elsewhere on the board
VIN+: CON-IN.1; also elsewhere on the board
Y5V0: CON-OUT.6; also elsewhere on the board
Y5V2: CON-OUT.2; also elsewhere on the board
Y5V8: CON-OUT.4; also elsewhere on the board

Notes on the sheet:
Connectors

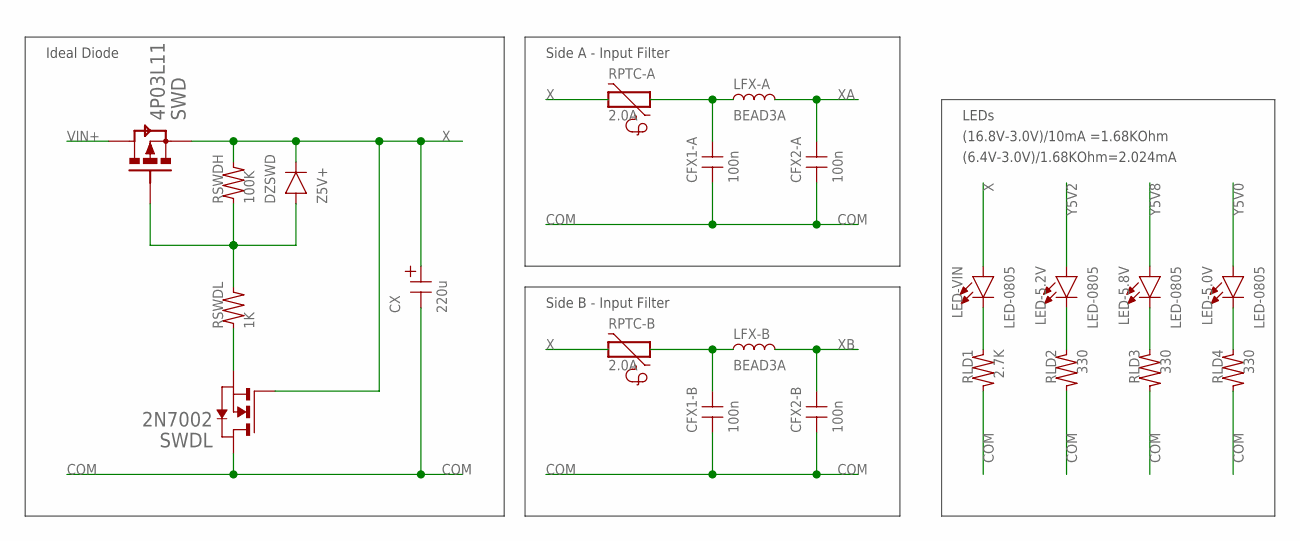
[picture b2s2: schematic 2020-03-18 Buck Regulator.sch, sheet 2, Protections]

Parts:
CFX1-A, CFX1-B, CFX2-A, CFX2-B: 100n; SMD0805
CX: 220u; CPOL-5MM5
DZSWD: Z5V+; SMD0805-POL
LED-5.0V, LED-5.2V, LED-5.8V: LED-0805; SMD0805-POL
LED-VIN: LED-0805; SMD0805-POL
LFX-A: BEAD3A; SMD2MM0X1MM60
LFX-B: BEAD3A; SMD2MM0X1MM60
RLD1: 2.7K; SMD0805
RLD2, RLD3, RLD4: 330; SMD0805
RPTC-A: 2.0A; M0805
RPTC-B: 2.0A; M0805
RSWDH: 100K; SMD0805
RSWDL: 1K; SMD0805
SWD: 4P03L11; TO252
SWDL: 2N7002; SOT23

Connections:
COM: CFX1-A.2, CFX1-B.2, CFX2-A.2, CFX2-B.2, CX.-, RLD1.2, RLD2.2, RLD3.2, RLD4.2, SWDL.3 (D); also elsewhere on the board
unnamed: CFX1-A.1, LFX-A.1, RPTC-A.2
unnamed: DZSWD.+, RSWDH.1, RSWDL.2, SWD.1 (G)
unnamed: RSWDL.1, SWDL.2 (S)
unnamed: LED-VIN.-, RLD1.1
unnamed: LED-5.2V.-, RLD2.1
unnamed: LED-5.8V.-, RLD3.1
unnamed: LED-5.0V.-, RLD4.1
unnamed: CFX1-B.1, LFX-B.1, RPTC-B.2
VIN+: SWD.3 (D); also elsewhere on the board
X: CX.+, DZSWD.-, LED-VIN.+, RPTC-A.1, RPTC-B.1, RSWDH.2, SWD.2 (S), SWDL.1 (G)
XA: CFX2-A.1, LFX-A.2; also elsewhere on the board
XB: CFX2-B.1, LFX-B.2; also elsewhere on the board
Y5V0: LED-5.0V.+; also elsewhere on the board
Y5V2: LED-5.2V.+; also elsewhere on the board
Y5V8: LED-5.8V.+; also elsewhere on the board

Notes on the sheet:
Ideal Diode
Side A - Input Filter
Side B - Input Filter
LEDs
(16.8V-3.0V)/10mA =1.68KOhm
(6.4V-3.0V)/1.68KOhm=2.024mA

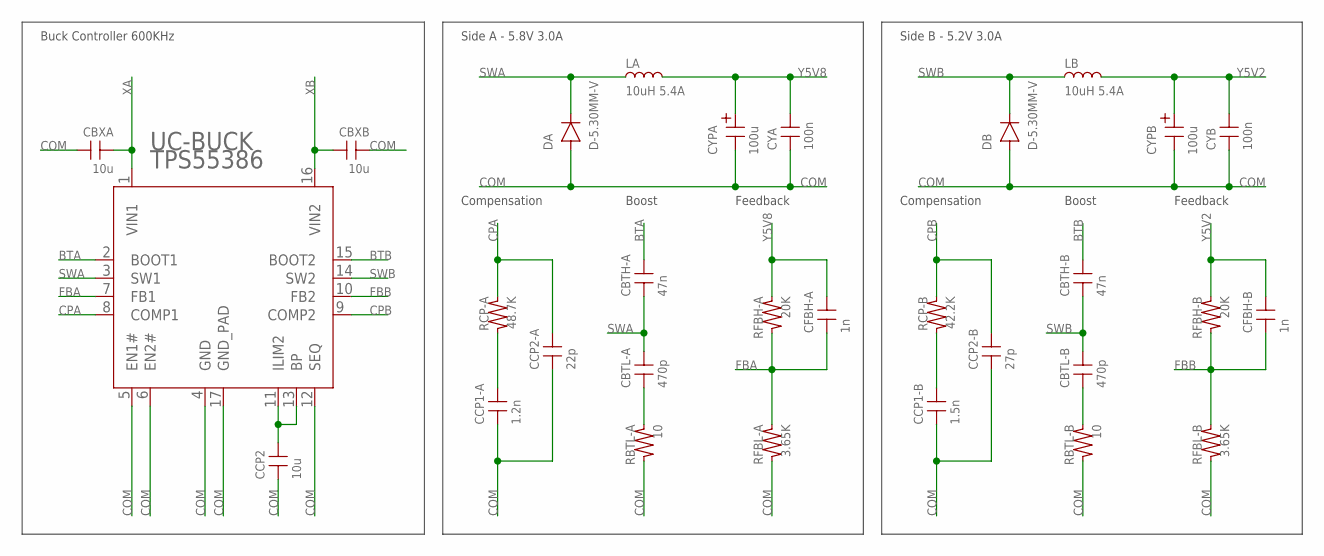
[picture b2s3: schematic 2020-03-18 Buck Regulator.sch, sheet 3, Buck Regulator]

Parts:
CBTH-A: 47n; SMD0805
CBTH-B: 47n; SMD0805
CBTL-A: 470p; SMD0805
CBTL-B: 470p; SMD0805
CBXA: 10u; SMD3MM2X1MM60
CBXB: 10u; SMD3MM2X1MM60
CCP1-A: 1.2n; SMD0805
CCP1-B: 1.5n; SMD0805
CCP2: 10u; SMD3MM2X1MM60
CCP2-A: 22p; SMD0805
CCP2-B: 27p; SMD0805
CFBH-A: 1n; SMD0805
CFBH-B: 1n; SMD0805
CYA: 100n; SMD0805
CYB: 100n; SMD0805
CYPA: 100u; CPOL-5MM5
CYPB: 100u; CPOL-5MM5
DA: D-5.30MM-V; THV-5MM30
DB: D-5.30MM-V; THV-5MM30
LA: 10uH 5.4A; SMD12MM8X12MM8
LB: 10uH 5.4A; SMD12MM8X12MM8
RBTL-A: 10; SMD0805
RBTL-B: 10; SMD0805
RCP-A: 48.7K; SMD0805
RCP-B: 42.2K; SMD0805
RFBH-A: 20K; SMD0805
RFBH-B: 20K; SMD0805
RFBL-A: 3.65K; SMD0805
RFBL-B: 3.65K; SMD0805
UC-BUCK: TPS55386; HTSSOP16

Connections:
BTA: CBTH-A.1, UC-BUCK.2 (BOOT1)
BTB: CBTH-B.1, UC-BUCK.15 (BOOT2)
COM: CBXA.1, CBXB.2, CCP1-A.2, CCP1-B.2, CCP2.2, CCP2-A.2, CCP2-B.2, CYA.2, CYB.2, CYPA.-, CYPB.-, DA.+, DB.+, RBTL-A.2, RBTL-B.2, RFBL-A.2, RFBL-B.2, UC-BUCK.4 (GND), UC-BUCK.5 (EN1#), UC-BUCK.6 (EN2#), UC-BUCK.12 (SEQ), UC-BUCK.17 (GND_PAD); also elsewhere on the board
CPA: CCP2-A.1, RCP-A.1, UC-BUCK.8 (COMP1)
CPB: CCP2-B.1, RCP-B.1, UC-BUCK.9 (COMP2)
FBA: CFBH-A.2, RFBH-A.2, RFBL-A.1, UC-BUCK.7 (FB1)
FBB: CFBH-B.2, RFBH-B.2, RFBL-B.1, UC-BUCK.10 (FB2)
unnamed: CBTL-A.2, RBTL-A.1
unnamed: CCP2.1, UC-BUCK.11 (ILIM2), UC-BUCK.13 (BP)
unnamed: CCP1-A.1, RCP-A.2
unnamed: CCP1-B.1, RCP-B.2
unnamed: CBTL-B.2, RBTL-B.1
SWA: CBTH-A.2, CBTL-A.1, DA.-, LA.1, UC-BUCK.3 (SW1)
SWB: CBTH-B.2, CBTL-B.1, DB.-, LB.1, UC-BUCK.14 (SW2)
XA: CBXA.2, UC-BUCK.1 (VIN1); also elsewhere on the board
XB: CBXB.1, UC-BUCK.16 (VIN2); also elsewhere on the board
Y5V2: CFBH-B.1, CYB.1, CYPB.+, LB.2, RFBH-B.1; also elsewhere on the board
Y5V8: CFBH-A.1, CYA.1, CYPA.+, LA.2, RFBH-A.1; also elsewhere on the board

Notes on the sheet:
Side A - 5.8V 3.0A
Buck Controller 600KHz
Compensation
Boost
Feedback
Side B - 5.2V 3.0A

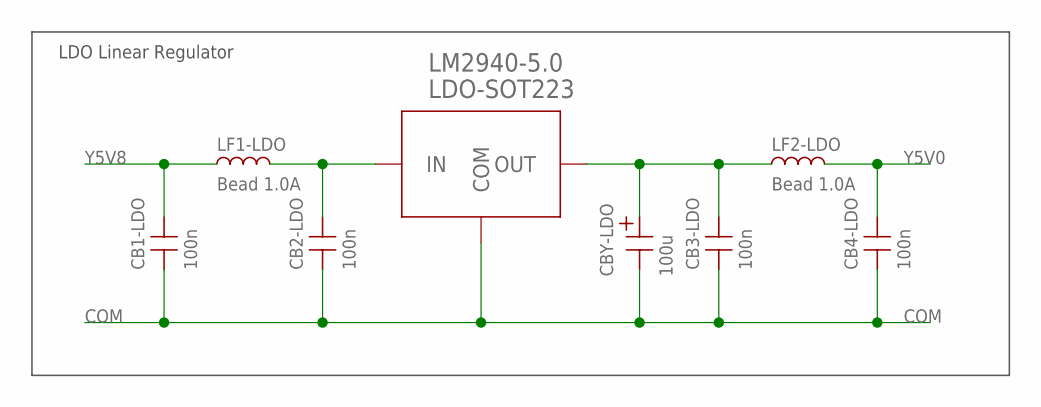
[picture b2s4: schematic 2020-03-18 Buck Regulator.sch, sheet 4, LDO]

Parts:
CB1-LDO, CB2-LDO, CB3-LDO, CB4-LDO: 100n; SMD0805
CBY-LDO: 100u; CPOL-5MM5
LF1-LDO, LF2-LDO: Bead 1.0A; SMD0805
LM2940-5.0: LDO-SOT223; SOT223

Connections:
COM: CB1-LDO.2, CB2-LDO.2, CB3-LDO.2, CB4-LDO.2, CBY-LDO.-, LM2940-5.0.2 (COM), LM2940-5.0.4 (COM); also elsewhere on the board
unnamed: CB3-LDO.1, CBY-LDO.+, LF2-LDO.1, LM2940-5.0.3 (OUT)
unnamed: CB2-LDO.1, LF1-LDO.2, LM2940-5.0.1 (IN)
Y5V0: CB4-LDO.1, LF2-LDO.2; also elsewhere on the board
Y5V8: CB1-LDO.1, LF1-LDO.1; also elsewhere on the board

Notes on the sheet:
LDO Linear Regulator

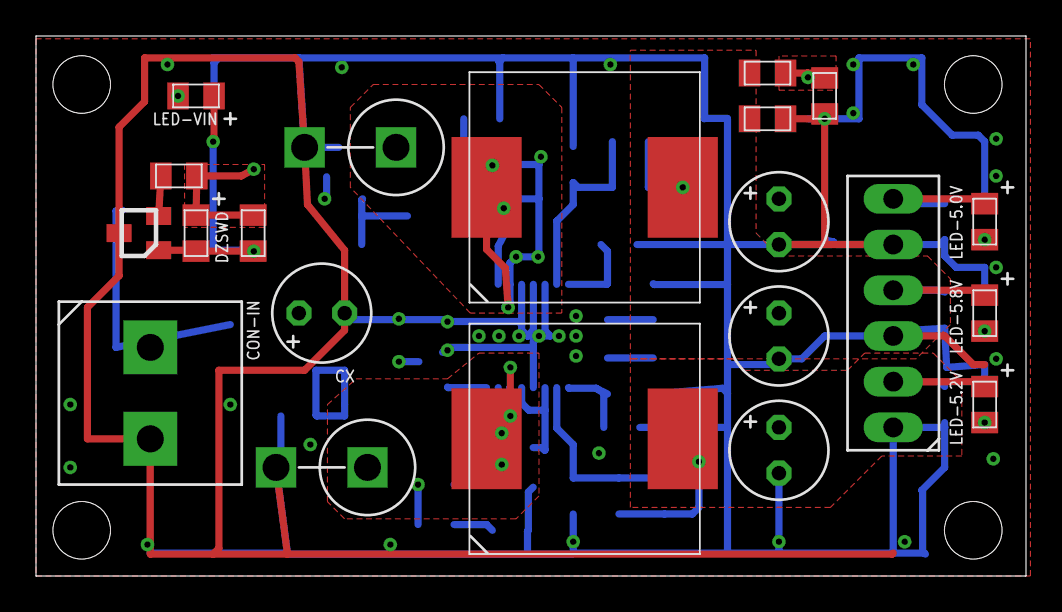
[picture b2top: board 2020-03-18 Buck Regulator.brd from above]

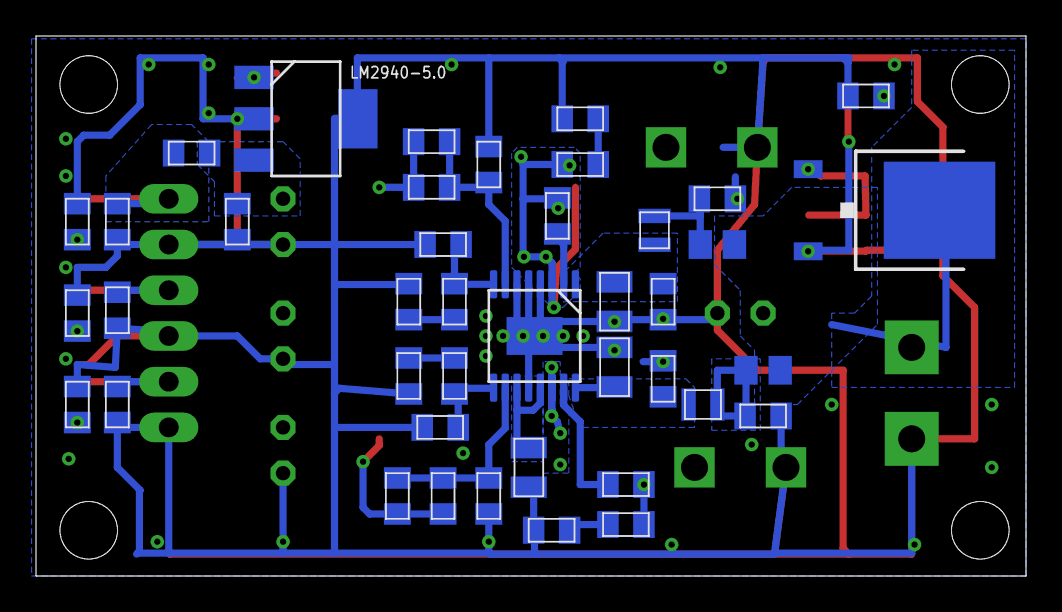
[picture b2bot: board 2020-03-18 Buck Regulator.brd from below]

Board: 2 copper layers, 55.0 x 30.0 mm, 64 parts (41 on the bottom side), 31 nets.

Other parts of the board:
U$1: SIGNATURE_ORANGEBOT_SMALL
U$2: SIGNATURE_ADROBOT_SMALL

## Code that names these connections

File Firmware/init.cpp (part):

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
	//----------------------------------------------------------------
	//!	PORTA
	//!	PA0				: UART0 TXO
	//!	PA1				: UART0 RXI
	//!	PA2, TCB0		: 
	//!	PA3, TCB1		: 
	//!	PA4				: 
	//!	PA5				: 
	//!	PA6				: UC_BTN
	//!	PA7				: LCD PWR#
	//----------------------------------------------------------------
	//				0		1		2		3		4		5		6		7
	PORT_A_CONFIG(	PIN_H,	PIN_R,	PIN_Z,	PIN_Z,	PIN_Z,	PIN_Z,	PIN_R,	PIN_H );

	//----------------------------------------------------------------
	//!	PORTB
	//!	PB0,			: LCD D4
	//!	PB1,			: LCD D5
	//!	PB2				: LCD D6
	//!	PB3				: LCD D7
	//!	PB4,			: LCD EN
	//!	PB5,			: LCD RS
	//!	PB6				:
	//!	PB7				:
	//----------------------------------------------------------------
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
	//----------------------------------------------------------------
	//!	PORTC
	//!	PC0				:
	//!	PC1				:
	//!	PC2				:
	//!	PC3				:
	//!	PC4				: UC_LED0 (GREEN)
	//!	PC5				: UC_LED1 (BLUE)
	//!	PC6				:
	//!	PC7				:
	//----------------------------------------------------------------
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
	//----------------------------------------------------------------
	//!	PORTD
	//!	PD0, ADC		: 
	//!	PD1, ADC		: 
	//!	PD2, ADC		: 
	//!	PD3, ADC		: 
	//!	PD4				:
	//!	PD5				:
	//!	PD6				: 
	//!	PD7				:	UC_SERVO_POWER#	| false = allow power to flow from the regulator channel 2 to the servo connectors
	//----------------------------------------------------------------
	//				0		1		2		3		4		5		6		7
	PORT_D_CONFIG(	PIN_Z,	PIN_Z,	PIN_Z,	PIN_Z,	PIN_Z,	PIN_Z,	PIN_Z,	PIN_H );

	//----------------------------------------------------------------
	//!	PORTE
	//!	PE0				: SERVO1
	//!	PE1				: SERVO2
	//!	PE2				: SERVO3
	//!	PE3				: SERVO4
	//!	PE4				: 
	//!	PE5				: 
	//!	PE6				: 
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
	//----------------------------------------------------------------
	//!	PORTF
	//!	PF0				: SERVO5
	//!	PF1				: SERVO6
	//!	PF2				: SERVO7
	//!	PF3				: SERVO8
	//!	PF4				: 
	//!	PF5				: 
	//!	PF6				:
	//!	PF7				:
	//----------------------------------------------------------------
	//				0		1		2		3		4		5		6		7
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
